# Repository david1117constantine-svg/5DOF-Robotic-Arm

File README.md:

# 5DOF-Robotic-Arm

This repository is for my very first Hack Club Blueprint Grant Submission, along with anyone else who wants to watch my progress and build their own 5DOF robot arm.

## Overview
* ESP32-S3
* A4988 Drivers
* Nema 17 Stepper Motors
* 25:1 Strain Wave Gearbox *Credit to @user_454693624 over on Makerworld (More Details in CAD Directory)*

## WHY?
This is the first passion project of mine that I have actually pursued. I love engineering, building computers, and 3d printing. All these hobbies have led to this monstrosity of an endeavour. This arm is meant to be modular, easily printable, and fairly inexpensive for hobbyists to build on their own and tinker with. This project has definitely challenged me in ways I couldn't imagine. I started, naive to the oncoming money pit that the thing would become. That's why I am so thankful to the amazing folks over at Blueprint and Hackclub for supporting students in their pursuit of engineering.

## How Does it Work?
This 5DOF Arm is powered by 5 NEMA 17 34mm 0.35A 12V 1.8deg Stepper Motors that you can find at many online stores, such as StepperOnline or, in my case, Adafruit. The joints in the shoulder, elbow, and wrist pitch axis all use the same gearbox and housing assemblies, making for simpler printing and a common attachment point for new structural designs. You might notice there is no end effector piece on this Arm, and that is intentional. The PCB has two servo headers that can be utilized for many different Griper or Claw style designs, or maybe a suction cup or magnet, who knows the possibilities. The PCB is also made for simple installations, simply requiring you to insert your ESP32, motor drivers, servos, etc.

## How To Use It?
One of the major design philosophies behind this project was to build a platform that could be used to test different control mechanisms. As I wrote in the blueprint submission page, I plan to attempt control with a BCI device if I can get my hands on one. To set up the arm, compile and upload the firmware with Arduino IDE, and plug the board into the PCB. I suggest running the code over USB to get a serial output, this will provide you with an IP which you can go to and control the Arm over wifi with the device of your choice. *Note you must replace the SSID and PASSWORD fields with your wifi credentials to let the board connect to wifi. The web GUI is fairly straightforward with multiple ways of interacting with the arm, whether that be individual joint movements or Cartesian Coordinates, though the IK solver has not been refined enough yet for that system to work as intended.

## PCB: Schematic, Footprints, and Renders

#### Schematic:

#### Footprint:

#### Render:

## More Photos:

## BOM
| Item                                                    | Quantity   | Total Price ($)   | Link                                                                                                                                                                     |
|:--------------------------------------------------------|:-----------|:------------------|:-------------------------------------------------------------------------------------------------------------------------------------------------------------------------|
| Self-Sourced                                            |            |                   |                                                                                                                                                                          |
| Screws - Assorted M3                                    | 2240       | Self-Sourced      |                                                                                                                                                                          |
| Bearing - 6807 2RS                                      | 5          | Self-Sourced      | [Link](https://www.amazon.com/XIKE-6807-2RS-Bearings-35x47x7mm-Pre-Lubricated/dp/B09D2ZHNPH/ref=sr_1_4)                                                                   |
| Microcontroller - ESP32                                 | 1          | Self-Sourced      | [Link](https://www.aliexpress.us/item/3256809776335245.html)                                                                                                              |
| Electronics (Exluding PCB)                              |            |                   |                                                                                                                                                                          |
| Stepper motor - NEMA-17 size - 200 steps/rev, 12V 350mA | 5          | 70.00             | [Link](https://www.google.com/search?q=NEMA+17+stepper+motor)                                                                                                            |
| Stepper Motor Driver - A4988                            | 5          | 3.66              | [Link](https://www.aliexpress.us/item/3256808219893938.html)                                                                                                              |
| Limit Switch                                            | 3          | 0.41              | [Link](https://www.lcsc.com/product-detail/C50395955.html)                                                                                                               |
| Buck Converter - 12v to 5v, 5A                          | 1          | 2.98              | [Link](https://www.aliexpress.us/item/3256810527502423.html)                                                                                                              |
| Wire Connectors - JST xh 2.54 2Pin 10pcs                | 1          | 1.39              | [Link](https://www.aliexpress.us/item/3256808413328991.html)                                                                                                              |
| Wire Connectors - JST xh 2.54 4Pin 10pcs                | 1          | 1.86              | [Link](https://www.aliexpress.us/item/3256808413328991.html)                                                                                                              |
| Wire - General Purpose 28 Gauge Wire                    | 1          | 9.28              | [Link](https://www.aliexpress.us/item/3256805264336680.html)                                                                                                              |
| Heat Shrink Tubing - 5mm ID, 5M                         | 1          | 3.28              | [Link](https://www.aliexpress.us/item/3256806019046145.html)                                                                                                              |
| Power Supply - DC12V 8A                                 | 1          | 15.43             | [Link](https://www.aliexpress.us/item/3256801543468653.html)                                                                                                              |
| Hardware                                                |            |                   |                                                                                                                                                                          |
| Extrutions - 150mm 2020 T-slot Extrutions 4pcs          | 4          | 18.05             | [Link](https://www.aliexpress.us/item/3256808366074196.html)                                                                                                              |
| Screws - M4x10 Countersunk                              | 4          | 0.02              | [Link](https://jlcmc.com/product/s/E02/EDLJ/din-7991-gb-t-70.3-hex-socket-countersunk-head-screw)                                                                        |
| Screws - M4x16 BHCS                                     | 8          | 0.09              | [Link](https://jlcmc.com/product/s/E02/EDLG/iso-7380-hex-socket-button-head-screw)                                                                                       |
| T-Nuts - M4 20 Series Profile                           | 12         | 0.09              | [Link](https://jlcmc.com/product/s/T02/TPAA/m3-m4-m5-t-nut-20-series-aluminum-profile-fasteners)                                                                         |
| Heat Inserts - M3x4x5                                   | 100        | 4.18              | [Link](https://www.aliexpress.us/item/3256807712431371.html)                                                                                                              |
| NEMA 17 Strain Wave Gearbox (OpenSource) BOM            |            |                   | [Link](https://makerworld.com/en/models/1303481-nema-17-strain-wave-gearbox#profileId-1336298)                                                                           |
| Bearings  - 6706 2RS                                    | 5          | 4.35              | [Link](https://www.aliexpress.us/item/3256806677694798.html)                                                                                                              |
| Bearings - 605ZZ                                        | 10         | 0.99              | [Link](https://www.aliexpress.us/item/3256801622664412.html)                                                                                                              |
| Bearings - 4mm Balls                                    | 200        | 6.28              | [Link](https://www.aliexpress.us/item/3256807297992129.html)                                                                                                              |
| PCB Components                                          |            |                   |                                                                                                                                                                          |
| Capacitor - 100uF 16V Capacitor                         | 5          | 0.70              | [Link](https://www.lcsc.com/product-detail/C31190.html)                                                                                                                  |
| Capacitor - 0.1uF Capacitor                             | 5          | 0.67              | [Link](https://www.lcsc.com/product-detail/C1620282.html)                                                                                                                  |
| Capacitor - 47uF                                        | 1          | 0.90              | [Link](https://www.lcsc.com/product-detail/C3540.html)                                                                                                                   |
| Capacitor - 1000uF                                      | 2          | 1.33              | [Link](https://www.lcsc.com/product-detail/C31154.html)                                                                                                                  |
| Screw Terminal - 2 Pin                                  | 3          | 1.04              | [Link](https://www.aliexpress.us/item/2251832049646879.html)                                                                                                              |
| Schottky Diode - 1N5819                                 | 2          | 0.06              | [Link](https://www.lcsc.com/product-detail/C2132.html)                                                                                                                   |
| Female Pin Headers - 1x22                               | 2          | 0.80              | [Link](https://www.lcsc.com/product-detail/C474775.html)                                                                                                                 |
| Female Pin Headers - 1x8                                | 10         | 0.59              | [Link](https://www.aliexpress.us/item/3256804116522266.html)                                                                                                              |

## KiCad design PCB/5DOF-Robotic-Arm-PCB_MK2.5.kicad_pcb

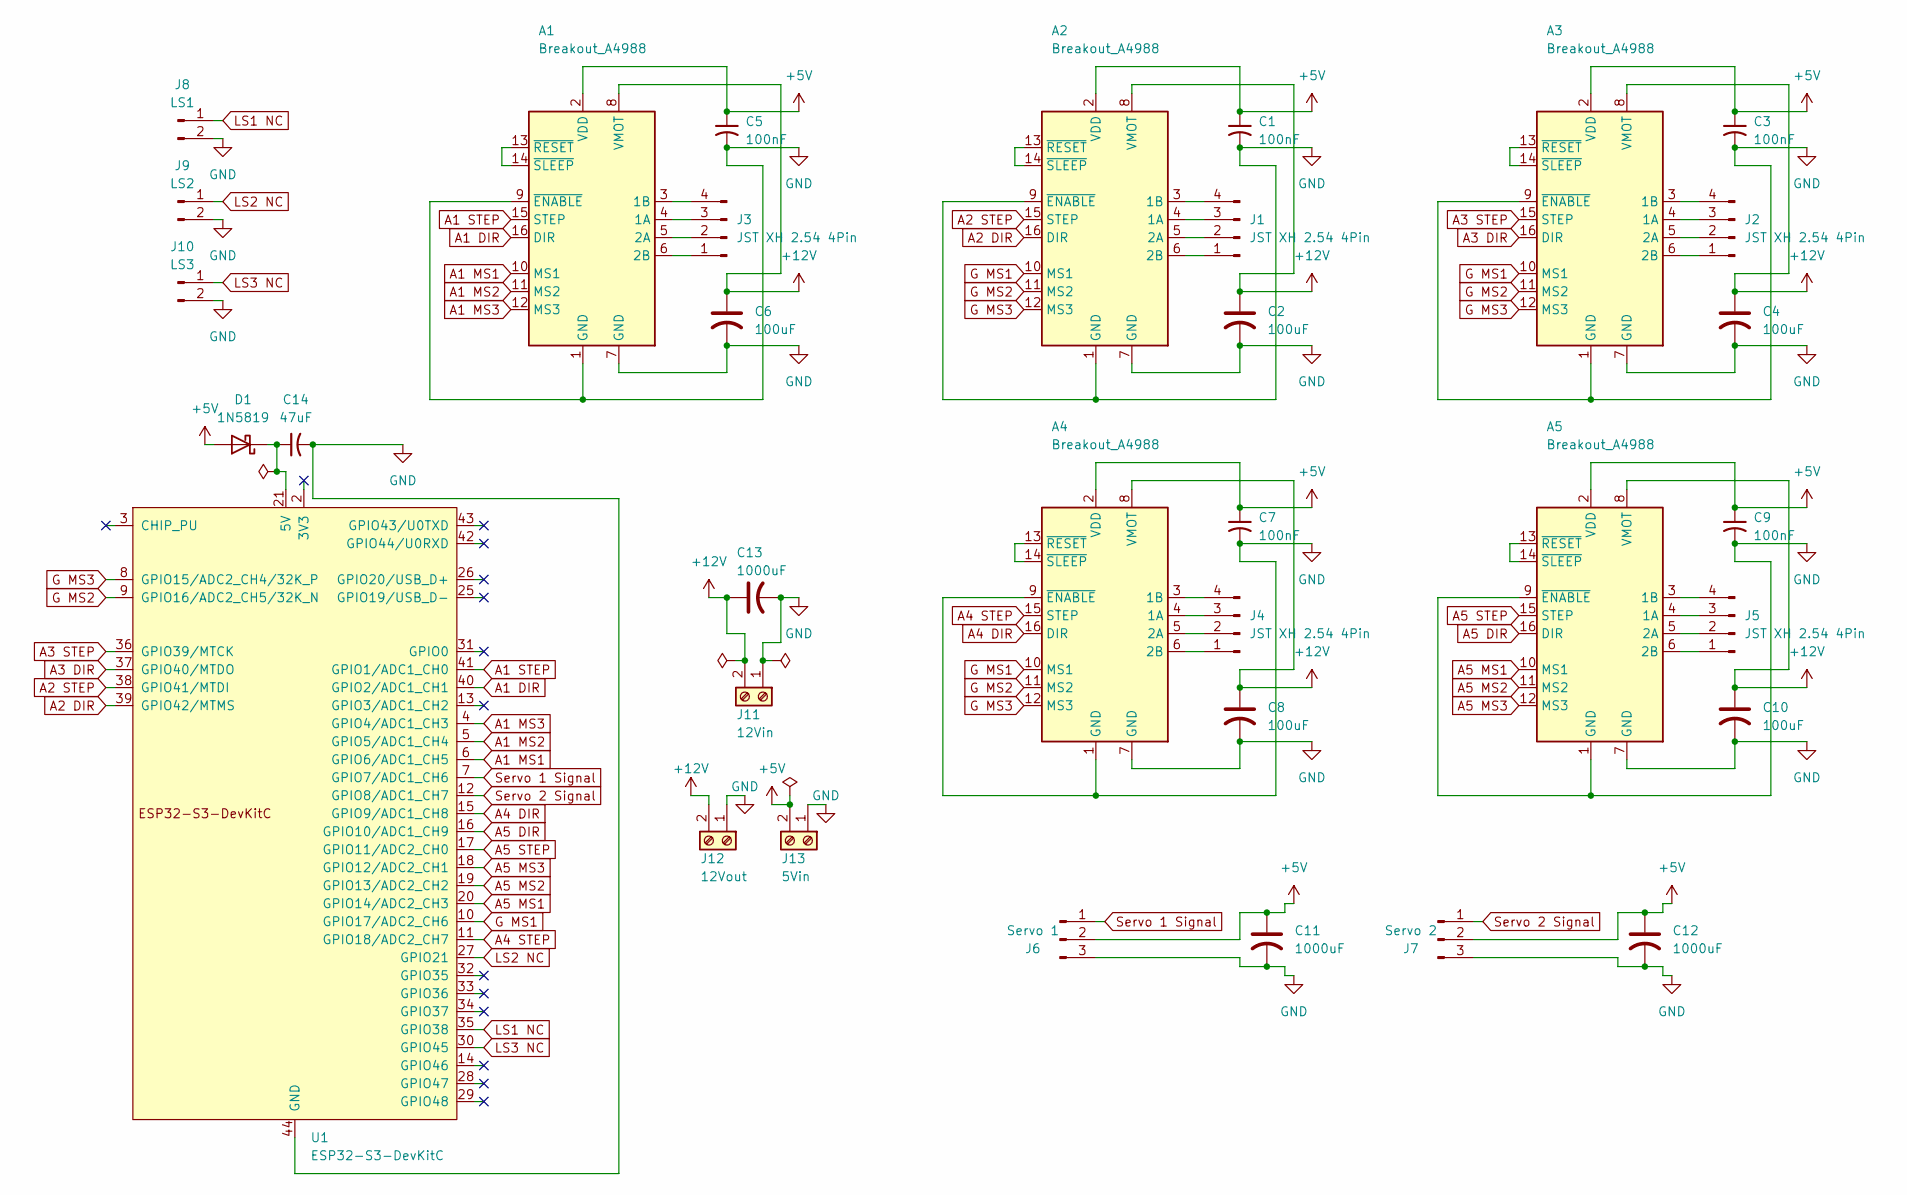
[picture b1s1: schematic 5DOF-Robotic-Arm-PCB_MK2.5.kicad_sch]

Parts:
A1, A2, A3, A4, A5: Breakout_A4988; Pololu_Breakout-16_15.2x20.3mm
C1, C3, C5, C7, C9: 100nF; C_Disc_D3.0mm_W1.6mm_P2.50mm
C2, C4, C6, C8, C10: 100uF; C_Radial_D5.0mm_H7.0mm_P2.00mm
C11, C12, C13: 1000uF; C_Radial_D10.0mm_H16.0mm_P5.00mm
C14: 47uF; C_Radial_D4.0mm_H7.0mm_P1.50mm
D1: 1N5819; D_DO-41_SOD81_P10.16mm_Horizontal
J1, J2, J3, J4, J5: JST XH 2.54 4Pin; JST_XH_B4B-XH-A_1x04_P2.50mm_Vertical
J6: Servo 1; PinHeader_1x03_P2.54mm_Vertical
J7: Servo 2; PinHeader_1x03_P2.54mm_Vertical
J8: LS1; JST_XH_B2B-XH-A_1x02_P2.50mm_Vertical
J9: LS2; JST_XH_B2B-XH-A_1x02_P2.50mm_Vertical
J10: LS3; JST_XH_B2B-XH-A_1x02_P2.50mm_Vertical
J11: 12Vin; TerminalBlock_Phoenix_MPT-0,5-2-2.54_1x02_P2.54mm_Horizontal
J12: 12Vout; TerminalBlock_Phoenix_MPT-0,5-2-2.54_1x02_P2.54mm_Horizontal
J13: 5Vin; TerminalBlock_Phoenix_MPT-0,5-2-2.54_1x02_P2.54mm_Horizontal
U1: ESP32-S3-DevKitC

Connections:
+5V: A1.2 (VDD), A2.2 (VDD), A3.2 (VDD), A4.2 (VDD), A5.2 (VDD), C1.1, C3.1, C5.1, C7.1, C9.1, C11.1, C12.1, D1.2 (A), J6.2, J7.2, J13.2
+12V: A1.8 (VMOT), A2.8 (VMOT), A3.8 (VMOT), A4.8 (VMOT), A5.8 (VMOT), C2.1, C4.1, C6.1, C8.1, C10.1, C13.1, J11.2, J12.2
A1 DIR: A1.16 (DIR), U1.40 (GPIO2/ADC1_CH1)
A1 MS1: A1.10 (MS1), U1.6 (GPIO6/ADC1_CH5)
A1 MS2: A1.11 (MS2), U1.5 (GPIO5/ADC1_CH4)
A1 MS3: A1.12 (MS3), U1.4 (GPIO4/ADC1_CH3)
A1 STEP: A1.15 (STEP), U1.41 (GPIO1/ADC1_CH0)
A2 DIR: A2.16 (DIR), U1.39 (GPIO42/MTMS)
A2 STEP: A2.15 (STEP), U1.38 (GPIO41/MTDI)
A3 DIR: A3.16 (DIR), U1.37 (GPIO40/MTDO)
A3 STEP: A3.15 (STEP), U1.36 (GPIO39/MTCK)
A4 DIR: A4.16 (DIR), U1.15 (GPIO9/ADC1_CH8)
A4 STEP: A4.15 (STEP), U1.11 (GPIO18/ADC2_CH7)
A5 DIR: A5.16 (DIR), U1.16 (GPIO10/ADC1_CH9)
A5 MS1: A5.10 (MS1), U1.20 (GPIO14/ADC2_CH3)
A5 MS2: A5.11 (MS2), U1.19 (GPIO13/ADC2_CH2)
A5 MS3: A5.12 (MS3), U1.18 (GPIO12/ADC2_CH1)
A5 STEP: A5.15 (STEP), U1.17 (GPIO11/ADC2_CH0)
G MS1: A2.10 (MS1), A3.10 (MS1), A4.10 (MS1), U1.10 (GPIO17/ADC2_CH6)
G MS2: A2.11 (MS2), A3.11 (MS2), A4.11 (MS2), U1.9 (GPIO16/ADC2_CH5/32K_N)
G MS3: A2.12 (MS3), A3.12 (MS3), A4.12 (MS3), U1.8 (GPIO15/ADC2_CH4/32K_P)
GND: A1.1 (GND), A1.7 (GND), A1.9 (~ENABLE), A2.1 (GND), A2.7 (GND), A2.9 (~ENABLE), A3.1 (GND), A3.7 (GND), A3.9 (~ENABLE), A4.1 (GND), A4.7 (GND), A4.9 (~ENABLE), A5.1 (GND), A5.7 (GND), A5.9 (~ENABLE), C1.2, C2.2, C3.2, C4.2, C5.2, C6.2, C7.2, C8.2, C9.2, C10.2, C11.2, C12.2, C13.2, C14.2, J6.3, J7.3, J8.2, J9.2, J10.2, J11.1, J12.1, J13.1, U1.22 (GND), U1.23 (GND), U1.24 (GND), U1.44 (GND)
LS1 NC: J8.1, U1.35 (GPIO38)
LS2 NC: J9.1, U1.27 (GPIO21)
LS3 NC: J10.1, U1.30 (GPIO45)
unnamed: A1.4 (1A), J3.3
unnamed: A1.3 (1B), J3.4
unnamed: A1.5 (2A), J3.2
unnamed: A1.6 (2B), J3.1
unnamed: A1.13 (~RESET), A1.14 (~SLEEP)
unnamed: A2.4 (1A), J1.3
unnamed: A2.3 (1B), J1.4
unnamed: A2.5 (2A), J1.2
unnamed: A2.6 (2B), J1.1
unnamed: A2.13 (~RESET), A2.14 (~SLEEP)
unnamed: A3.4 (1A), J2.3
unnamed: A3.3 (1B), J2.4
unnamed: A3.5 (2A), J2.2
unnamed: A3.6 (2B), J2.1
unnamed: A3.13 (~RESET), A3.14 (~SLEEP)
unnamed: A4.4 (1A), J4.3
unnamed: A4.3 (1B), J4.4
unnamed: A4.5 (2A), J4.2
unnamed: A4.6 (2B), J4.1
unnamed: A4.13 (~RESET), A4.14 (~SLEEP)
unnamed: A5.4 (1A), J5.3
unnamed: A5.3 (1B), J5.4
unnamed: A5.5 (2A), J5.2
unnamed: A5.6 (2B), J5.1
unnamed: A5.13 (~RESET), A5.14 (~SLEEP)
unnamed: C14.1, D1.1 (K), U1.21 (5V)
Servo 1 Signal: J6.1, U1.7 (GPIO7/ADC1_CH6)
Servo 2 Signal: J7.1, U1.12 (GPIO8/ADC1_CH7)

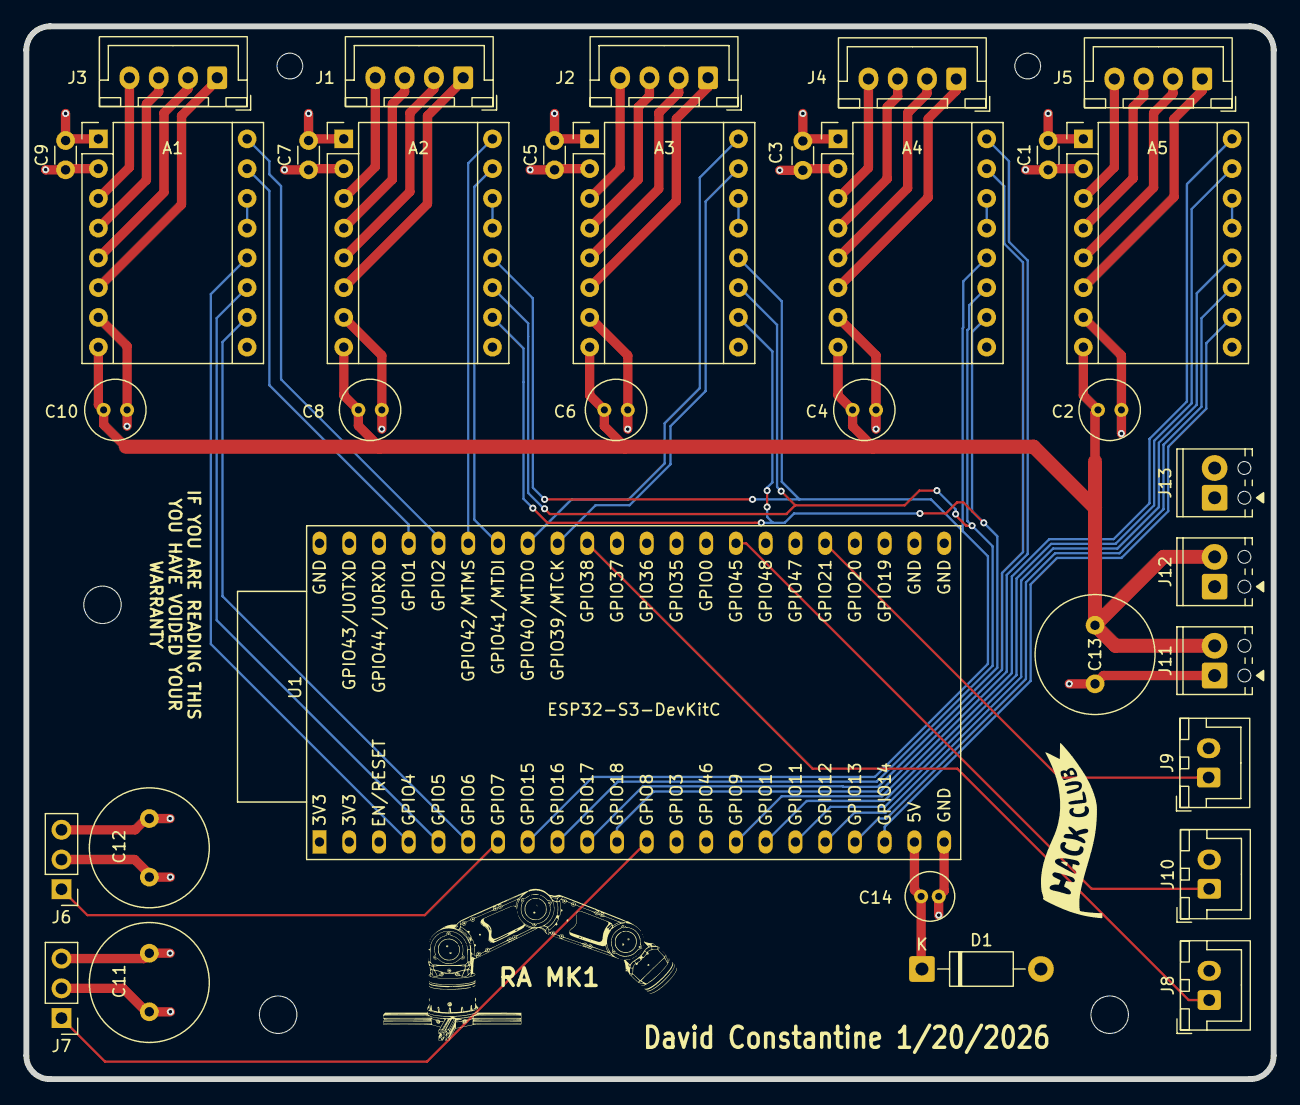
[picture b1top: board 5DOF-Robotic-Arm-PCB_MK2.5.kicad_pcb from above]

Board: 4 copper layers, 106.5 x 89.9 mm, 34 parts (0 on the bottom side), 53 nets.

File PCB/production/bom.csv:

Designator,Footprint,Quantity,Value,LCSC Part #
"A1, A2, A3, A4, A5",Pololu_Breakout-16_15.2x20.3mm,5,Breakout_A4988,
"C1, C3, C5, C7, C9",C_Disc_D3.0mm_W1.6mm_P2.50mm,5,100nF,
"C10, C2, C4, C6, C8",C_Radial_D5.0mm_H7.0mm_P2.00mm,5,100uF,
"C11, C12, C13",C_Radial_D10.0mm_H16.0mm_P5.00mm,3,1000uF,
C14,C_Radial_D4.0mm_H7.0mm_P1.50mm,1,47uF,
D1,D_DO-41_SOD81_P10.16mm_Horizontal,1,1N5819,
"J1, J2, J3, J4, J5",JST_XH_B4B-XH-A_1x04_P2.50mm_Vertical,5,JST XH 2.54 4Pin,
J10,JST_XH_B2B-XH-A_1x02_P2.50mm_Vertical,1,LS3,
J11,"TerminalBlock_Phoenix_MPT-0,5-2-2.54_1x02_P2.54mm_Horizontal",1,12Vin,
J12,"TerminalBlock_Phoenix_MPT-0,5-2-2.54_1x02_P2.54mm_Horizontal",1,12Vout,
J13,"TerminalBlock_Phoenix_MPT-0,5-2-2.54_1x02_P2.54mm_Horizontal",1,5Vin,
J6,PinHeader_1x03_P2.54mm_Vertical,1,Servo 1,
J7,PinHeader_1x03_P2.54mm_Vertical,1,Servo 2,
J8,JST_XH_B2B-XH-A_1x02_P2.50mm_Vertical,1,LS1,
J9,JST_XH_B2B-XH-A_1x02_P2.50mm_Vertical,1,LS2,
U1,ESP32-S3-DevKitC,1,ESP32-S3-DevKitC,

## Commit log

2026-01-08 Add description to README.md
    Added a brief description for the repository.
2026-01-08 Update README to invite collaboration on project
    Expanded description to include collaboration aspect.
2026-01-09 Create File
2026-01-09 Update README with current progress section
    Added a section for current progress and included an image.
2026-01-09 Fix image link formatting in README.md
2026-01-09 Correct image link in README
    Fix image link formatting in README.
2026-01-09 Rename Screenshot 2026-01-07 141455.png to PNG-1
2026-01-09 Update image in README with new screenshot
2026-01-09 Rename Screenshot 2026-01-07 141553.png to PNG_2
2026-01-09 Rename Screenshot 2026-01-07 141914.png to PNG_3
2026-01-09 Rename Screenshot 2026-01-07 142026.png to PNG_4
2026-01-09 Rename PNG-1 to PNG_1
2026-01-09 Fix image filename in README for consistency
2026-01-09 Revise README for project progress and motor issues
    Updated README with current progress and motor limitations.
2026-01-09 Rename PNG_1 to PNG_1.png
2026-01-09 Rename PNG_1.png to Image_1.png
2026-01-09 Rename PNG_2 to Image_2.png
2026-01-09 Rename PNG_3 to Image_3.png
2026-01-09 Rename PNG_4 to Image_4.png
2026-01-09 Fix image links and add stepper motor image
    Updated image references and added a new image for the stepper motors.
2026-01-09 Revise motor torque details and upgrade intentions
    Updated torque specifications and future plans for motor upgrades.
2026-01-09 Change project from 6DOF to 5DOF Robotic Arm
    Updated project title and description to reflect 5DOF.
2026-01-10 Add Journal Backlog for October 2025 to January 2026
2026-01-10 Add CC0 1.0 Universal license
2026-01-10 Rename Image_1.png to Image_1.png
2026-01-10 Rename Image_2.png to Image_2.png
2026-01-10 Rename Image_3.png to Image_3.png
2026-01-10 Rename Image_4.png to Image_4.png
2026-01-11 Added BOM
2026-01-11 Rename BOM file to 5DOF-Robotic-Arm_BOM.csv
2026-01-11 Rename BOM file to 5DOF-Robotic-Arm_BOMcsv
2026-01-11 Rename BOM file to correct CSV extension
2026-01-11 Rename BOM file for 5DOF Robotic Arm
2026-01-11 Rename Screenshot 2026-01-11 173757.png to Wiring/Wiring-Diagram.png
2026-01-13 Revise journal backlog with new entries and date
    Updated the date range and added new journal entries about the Voron project.
2026-01-13 Revise journal entries for Voron project updates
    Updated journal entries to reflect recent progress and excitement about the Voron 3D printer.
2026-01-14 Revise journal backlog with recent updates and images
    Updated journal backlog with new entries and images detailing the progress on the arm design and printing process.
2026-01-14 Add new journal entry for December 1, 2025
    Added a new entry about waist progress and design features.
2026-01-18 Add journal entry for December 4th, 2025
    Added a new entry for December 4th, 2025, to the journal backlog.
2026-01-20 Rename Master/Robotic_Arm_Master.f3z to CAD/Master/Robotic_Arm_Master.f3z
2026-01-20 Rename Master/Robotic_Arm_Master.step to CAD/Master/Robotic_Arm_Master.step
2026-01-25 Add 'WORK IN PROGRESS' section to BACKLOG.md
    Added a 'WORK IN PROGRESS' section to the backlog.
2026-01-25 Rename Robotic_Arm_Master.f3z to Robotic_Arm_Master.f3z
2026-01-25 Rename Robotic_Arm_Master.step to Robotic_Arm_Master.step
2026-01-25 Update Readme to include images description
    Added a brief description of the images in the Readme.
2026-01-25 Remove header from Images readme
    Removed header from the Images readme.
2026-01-25 Enhance README with project details and images
    Added project overview, motivation, and functionality details.
2026-01-25 Add PCB section to README with images
    Added PCB section with schematic, footprint, and render images.
2026-01-26 Rename IK_Solver.ino to Firmware/IK_Solver.ino
2026-01-26 Enhance BOM with Total Price column
    Added total price column to BOM for better cost tracking.
2026-01-26 Fix typos in BOM section of README.md
2026-01-27 Clarify PCB installation requirements in README
    Updated the description of the 5DOF Arm, clarifying installation requirements for the PCB and motors.
2026-01-28 Rename Credit.md to README.md
2026-01-28 Update README with credit and design link
    Added credit and link to original Strain-Wave Gearbox design.
2026-01-28 Update image in README for 5DOF Robotic Arm
2026-01-28 Update strain wave gearbox credit in README
    Added more details about the strain wave gearbox credit.
2026-01-28 Update BACKLOG.md with new journal entries
    Added new journal entries detailing progress on shoulder design and 3D printing updates.
2026-01-28 Revise BACKLOG.md for Upper Arm design updates
    Refined the description of the Upper Arm design and updated the text for clarity. Fixed minor grammatical errors and improved the flow of the narrative.
2026-01-28 Update BACKLOG.md with recent journal entries
    Added journal entries detailing project updates and funding opportunities.
2026-01-28 Add section for more photos in README
2026-01-28 Update README with new images and BOM section
    Added multiple images and a BOM section to the README.
2026-01-28 Remove unused image from README
    Removed an image from the README file.
2026-01-28 Add warning to README about untested code
    Added a warning about untested code and incomplete features.
2026-01-28 Replace WiFi credentials with placeholders
    Updated WiFi credentials to placeholders for security.
2026-01-28 Change WiFi credentials to placeholders
    Updated WiFi credentials for the web server.
2026-02-08 Revise BOM table with updated price details
    Updated BOM table to reflect changes in total price for items.
2026-02-15 Fix typos and update prices in README.md
2026-02-17 Add links to BOM items in README
    Updated the BOM table to include links for each item.
2026-02-17 Add usage instructions for the 5DOF Arm project
    Added a section on usage instructions for the 5DOF Arm project, detailing setup and control mechanisms.
2026-02-17 Update price for 0.1uF capacitor in README
    Updated the price for the 0.1uF capacitor to reflect the new cost.
